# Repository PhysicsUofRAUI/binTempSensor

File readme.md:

# Bin Temperature Sensor
This project is a gadget to monitor the temperature in a grain bin. This is important because when grain heats it can spoil and a farmer can lose lots of money. The current iteration is the cheapest when 4 bins are wired up and costs about $140 per bin. That cost can be contrasted with the current bin monitoring systems which can cost up to $5000 a bin. The next iteration will focus on lowering the per bin cost for when more than 4 bins are wired up, and the iteration after that will integrate Arduino Cloud into the project, so that all collected data can be stored for later use.

## Main Hardware
### Arduino MKR 1400
This will be the Arduino that will send the alerts to the farmer and possibly one day send data to the Arduino Cloud. At the moment the code is designed to be controlled soley by the MKR 1400, but in the next iteration it will recieve alerts from regular Arduinos.

### Temperature Sensor
The DHT 22 or the DFR0198 sensor is currently being used as the sensor. Three of them are needed to monitor one bin.

### RF Link kits
The next iteration of the code will have the MKR 1400 recieve alerts from regular Arduinos about the sensors in the regular Arduinos.

### Arduino Mega
This will be used in the second iteration to control the sensors in the bin and send the alerts or data to the MKR 1400. 

## Implementations
### Current Implementation
The current iteration is simple, and only uses the MKR 1400 and the DHT 22 sensors or DFR0198 sensors. It will connect to the cloud and will request data every 15 minutes and if the temperature has changed the cloud will be updated. The frequency of readings can be reduced to save on data charges. This iteration is using the code located in code/ArduinoCloud.

#### Cost
Below I will outline the cost of how much the current implementation would cost for four large bins (about 30ft high). If your bins are larger or smaller you would either need to buy more or less wire, but it should not change the cost that much. The price of the wire put in is what I have got, but your price will probably be different.

#### Hardware Costs
##### With AM2302
| Item            | Price of One                                                                                                            | Number Needed | Total Cost |
| ------------    |:-----------------------------------------------------------------------------------------------------------------------:| -------------:| ----------:|
| MKR 1400        | [$103.41](https://www.digikey.ca/en/products/detail/arduino/ABX00018/8135631)                                           | 1             | $103.41    |
| DHT 22          | [$21.81](https://www.digikey.ca/en/products/detail/adafruit-industries-llc/393/5356714?s=N4IgTCBcDaIIIFkAEYDMAGCBdAvkA) | 12            | $261.72    |
| Junction Box    | [$25.99](https://www.amazon.ca/gp/product/B075DJQJVY/ref=ppx_yo_dt_b_asin_title_o00_s00?ie=UTF8&psc=1)                  | 1             | $25.99     |
| Wire (per foot) | Varies                                                                                                                  | 300           | $95        |
| Hologram Sim    | [$5.00](https://store.hologram.io/store/)                                                                               | 1             | $5.00      |
| Total           |                                                                                                                         |               | $491.12    |

Note that shipping was not included for any of this.

#### With DFR0198
| Item            | Price of One                                                                                                            | Number Needed | Total Cost |
| ------------    |:-----------------------------------------------------------------------------------------------------------------------:| -------------:| ----------:|
| MKR 1400        | [$103.41](https://www.digikey.ca/en/products/detail/arduino/ABX00018/8135631)                                           | 1             | $103.41    |
| DFR0198         | [$10.03](https://www.digikey.ca/en/products/detail/dfrobot/DFR0198/7597054)                                             | 12            | $120.36    |
| Junction Box    | [$25.99](https://www.amazon.ca/gp/product/B075DJQJVY/ref=ppx_yo_dt_b_asin_title_o00_s00?ie=UTF8&psc=1)                  | 1             | $25.99     |
| Wire (per foot) | Varies                                                                                                                  | 300           | $95        |
| Hologram Sim    | [$5.00](https://store.hologram.io/store/)                                                                               | 1             | $5.00      |
| Total           |                                                                                                                         |               | $349.76    |

#### Monthly Costs
| Item            | Price                                                                                                           |
| --------------------- |:-----------------------------------------------------:|
| Arduino Cloud Account | [$9.00 CAD](https://store.arduino.cc/digital/create#) | 
| Hologram Data Costs   | $11.80 CAD                                            |
| Total                 | $20.8                                                 |

Note: The data charges will probably be lower since this was calculated on costs when there was no grain in the bin and the temperature varies wildly then.

### Future Improvements
#### RF Link kits
The Arduino Mega has 54 digital pins so it can control many more bins than the MKR 1400 can, however, it cannot connect to the network. The RF link kit will allow the Mega to communication with the MKR 1400 and the MKR 1400 will be able to communicate with the network and send alerts.

#### Email Alerts
This is currently the focus of the work and it will entail the MKR GSM sending data to a third party, possibly IFTTT, which will then send out an email alerting the farmer to a temperature rise. 

# Contributing
Please anyone feel free to contribute. It would especially be appreciated if people with more experience on the hardware related, people involved on farms (like me :smiley:) who have experience to what is really needed to help production and save bushels, and people with experience writing software for this type of hardware.

All this being said I do want to stress that those thinking they don't know anything about this, but are still interested in the project please at least contact. We have almost no-one here and even if people don't think it they always have some sort of skill that could be used.

# Final Remarks
Hopefully this project becomes a success and maybe more like could be made!

Thanks for reading all this!

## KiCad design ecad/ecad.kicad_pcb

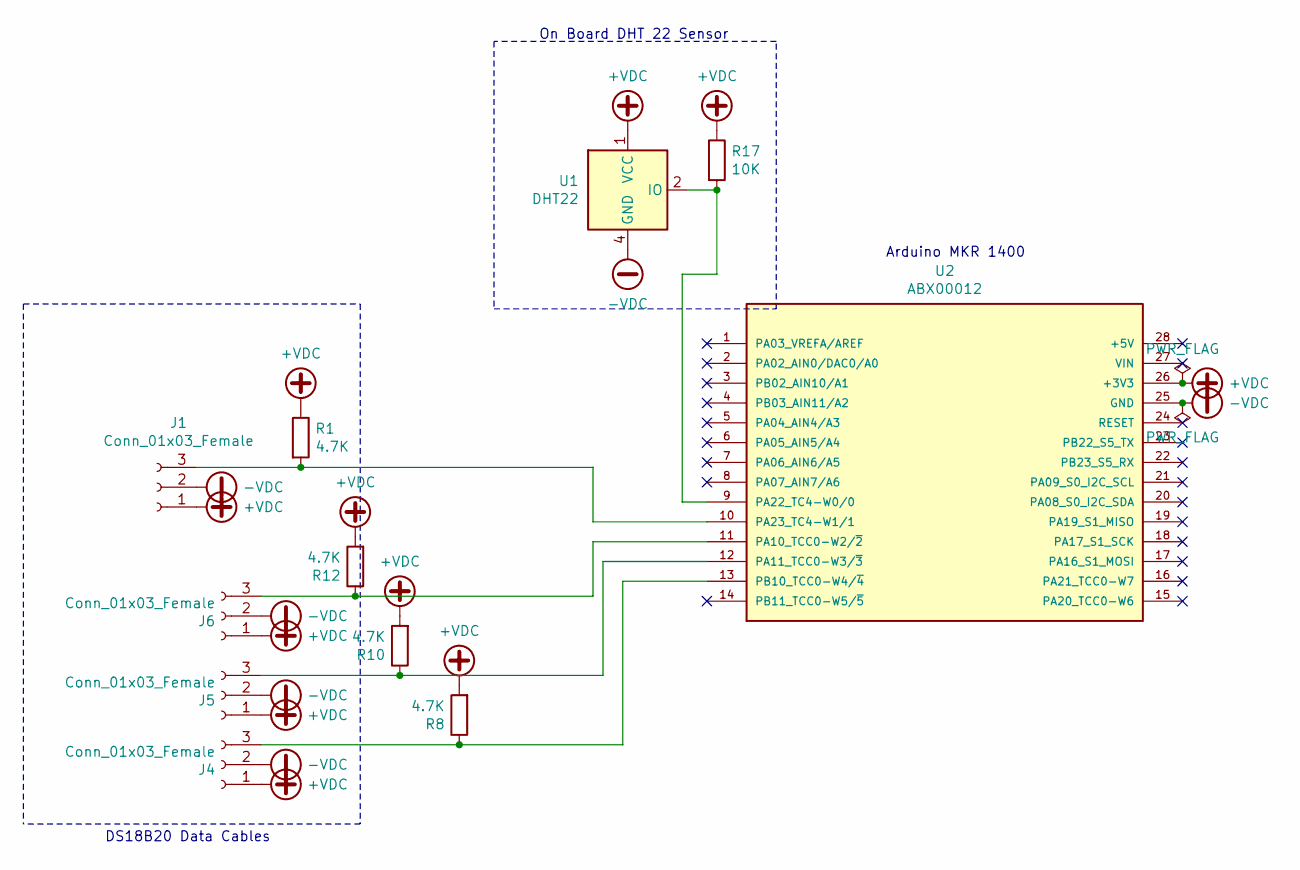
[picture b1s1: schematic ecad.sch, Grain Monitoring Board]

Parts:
J1, J4, J5, J6: Conn_01x03_Female; Wago_734-133_1x03_P5.0mm_Vertical
R1, R8, R10, R12: 4.7K; R_Axial_DIN0207_L6.3mm_D2.5mm_P7.62mm_Horizontal
R17: 10K; R_Axial_DIN0207_L6.3mm_D2.5mm_P7.62mm_Horizontal
U1: DHT22; Aosong_DHT11_5.5x12.0_P2.54mm
U2: ABX00012; ARDUINO_ABX00012; PARTREV 5

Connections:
+VDC: J1.1, J4.1, J5.1, J6.1, R1.1, R8.2, R10.2, R12.2, R17.1, U1.1 (VCC), U2.26 (+3V3)
-VDC: J1.2, J4.2, J5.2, J6.2, U1.4 (GND), U2.25 (GND)
unnamed: J1.3, R1.2, U2.10 (PA23_TC4-W1/1)
unnamed: J4.3, R8.1, U2.13 (PB10_TCC0-W4/~4)
unnamed: J5.3, R10.1, U2.12 (PA11_TCC0-W3/~3)
unnamed: J6.3, R12.1, U2.11 (PA10_TCC0-W2/~2)
unnamed: R17.2, U1.2 (IO), U2.9 (PA22_TC4-W0/0)

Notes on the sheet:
Arduino MKR 1400
DS18B20 Data Cables
On Board DHT 22 Sensor

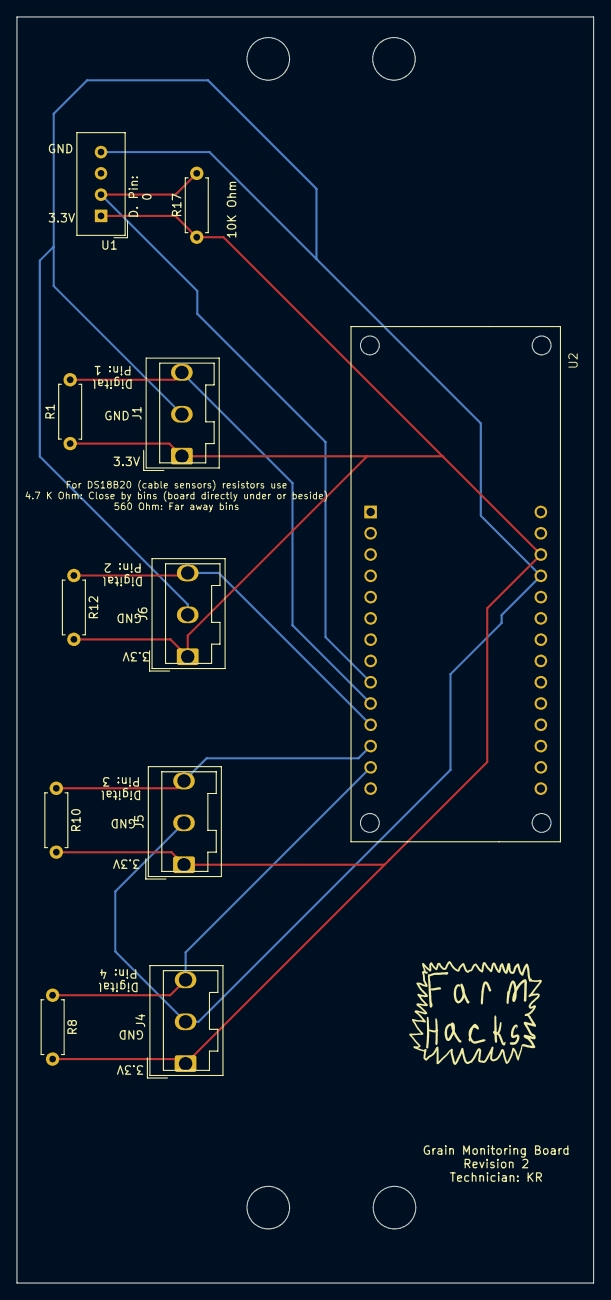
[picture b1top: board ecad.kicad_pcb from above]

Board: 2 copper layers, 68.8 x 151.1 mm, 11 parts (0 on the bottom side), 7 nets.

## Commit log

2018-08-02 Added readme
2018-08-02 Original Brainstorm notes
2018-10-06 First bit of code. Even if it does not work
2018-10-06 specified do not have way to select sensor
2018-12-04 Update readme.md
    Gave descriptions of three separate versions that could be made. Also added the talk about the DHT 22 sensor.
2018-12-31 made test code to retreive data from three sensors
2019-02-15 Updated readmes
2019-02-15 added new tutorial link
2019-02-17 code to control three sensors. Still need to add difference check
2019-02-17 added comments
2019-02-17 added tutorial links
2019-02-17 found some code on a tutorial that uses gsm module and the dht sensor
2019-02-17 code from tutorial being able to run from arduino editor
2019-06-09 made adjustments to github and added stuff
2019-06-09 axed that I will be making prototype this weekend
2019-06-09 removed base idea doc since it is outdated
2019-06-09 added a warning in the code folder
2019-06-24 archived a few files
2019-06-24 Created a test for battery and sensors. Updated relevant readme
2019-06-27 changeing the nan checking
2019-06-28 added low power code
2020-08-12 created a test to test the hardware
2020-10-25 reorgainized the repo
2020-10-27 code to monitor a single bin with three sensors
2020-10-29 code refactoring
2020-10-29 add gitignore
2020-10-30 created a mock libraray of DHT_U for testing custom library (#18)
2020-10-30 create custom library (#17)
2020-10-30 Add tests for the Mock DHT_U library (#18)
2020-10-30 Fix errors in the mock DHT_U library pointed out by the tests (#18)
2020-10-30 add tests for bin_sensor library (#18)
2020-10-30 Fix problems with bin_sensor library pointed out by the tests (#17)
2020-10-30 Use Approx function to make the tests involving floats better
2020-10-31 remove the archive
2020-10-31 add links to prices for four bins
2020-10-31 add document meant to explain how to use the custom library
2020-11-01 Add code to control one to four bins using the library
2020-11-01 create test using the new library
2020-11-01 create readme inside the code folder describing what all the code is
2020-11-01 actually this was the readme in the code directory
2020-12-31 deleted one uneeded comment
2021-01-24 drafted the temp cable tutorial
2021-01-30 added most of the photos to temperature cable tutorial
2021-01-30 added some code that will be used to test new temperature cables com uno
2021-02-01 added one more photo to the cable doc
2021-02-28 Added the two files that run the Arduino Cloud code
2021-02-28 add electrical schematic using the dfrobot temp probe in test
2021-02-28 add schematic using the dht11 sensor (temporary)
2021-04-09 update readme with cloud, DFR018 additions
2021-04-24 update code to send email alerts when temperature rises
2021-05-23 add files to create first iteration of pcb
2021-05-23 update gitignore to ignore uneeded pcb files
2021-06-04 add two bin code using ds18b20 sensors
2021-06-12 Update the AM2302 how-to doc.
2021-06-12 add more comments to the schematic
2021-07-23 add images to temperature cable doc
2021-07-23 update gitignore
2021-07-26 make pcb smaller and only one wire for each cable
2021-07-26 create initial DS18B20 cable tutorial.
2021-08-06 update ds18b20 temperature cable how to
2021-08-06 update pcb board
2021-08-06 add four bin code using the ds18b20 cables on the original pcb
2021-08-07 update 4 bin code solving minor bugs found while testing
2021-08-27 updated pcb to use 3.3V instead of 5V
2021-08-27 add some pcb files to gitignore
2021-08-27 switch from 5V to 3.3V
2021-08-28 add ds18b20 schematic
2021-12-17 added code to get temperatures on connection so zeros are not displayed
2021-12-17 removed the search for addresses since we will manually set them
2021-12-17 add pcb assembly doc
2021-12-17 update ds18b20 temp cable how-to
2021-12-17 add document showing process for collecting ds18b20 addresses
2021-12-19 update gitignore to include other gerber files
2021-12-19 add resistor values to silkscreen
2021-12-27 update and reorganize the how-to docs.
2021-12-27 update 4 bin 3 ds18b20 sensors per bin code.
2021-12-30 remove unnecessary code and picture
2021-12-30 add four ds18b20 and four bin code
2021-12-30 add full instruction booklet
2021-12-30 add upload code instruction booklet
2021-12-30 add antenna assembly booklet
2021-12-30 add forgotten photo pertaining to code instruction booklet
2022-01-08 add PCB only instructions
